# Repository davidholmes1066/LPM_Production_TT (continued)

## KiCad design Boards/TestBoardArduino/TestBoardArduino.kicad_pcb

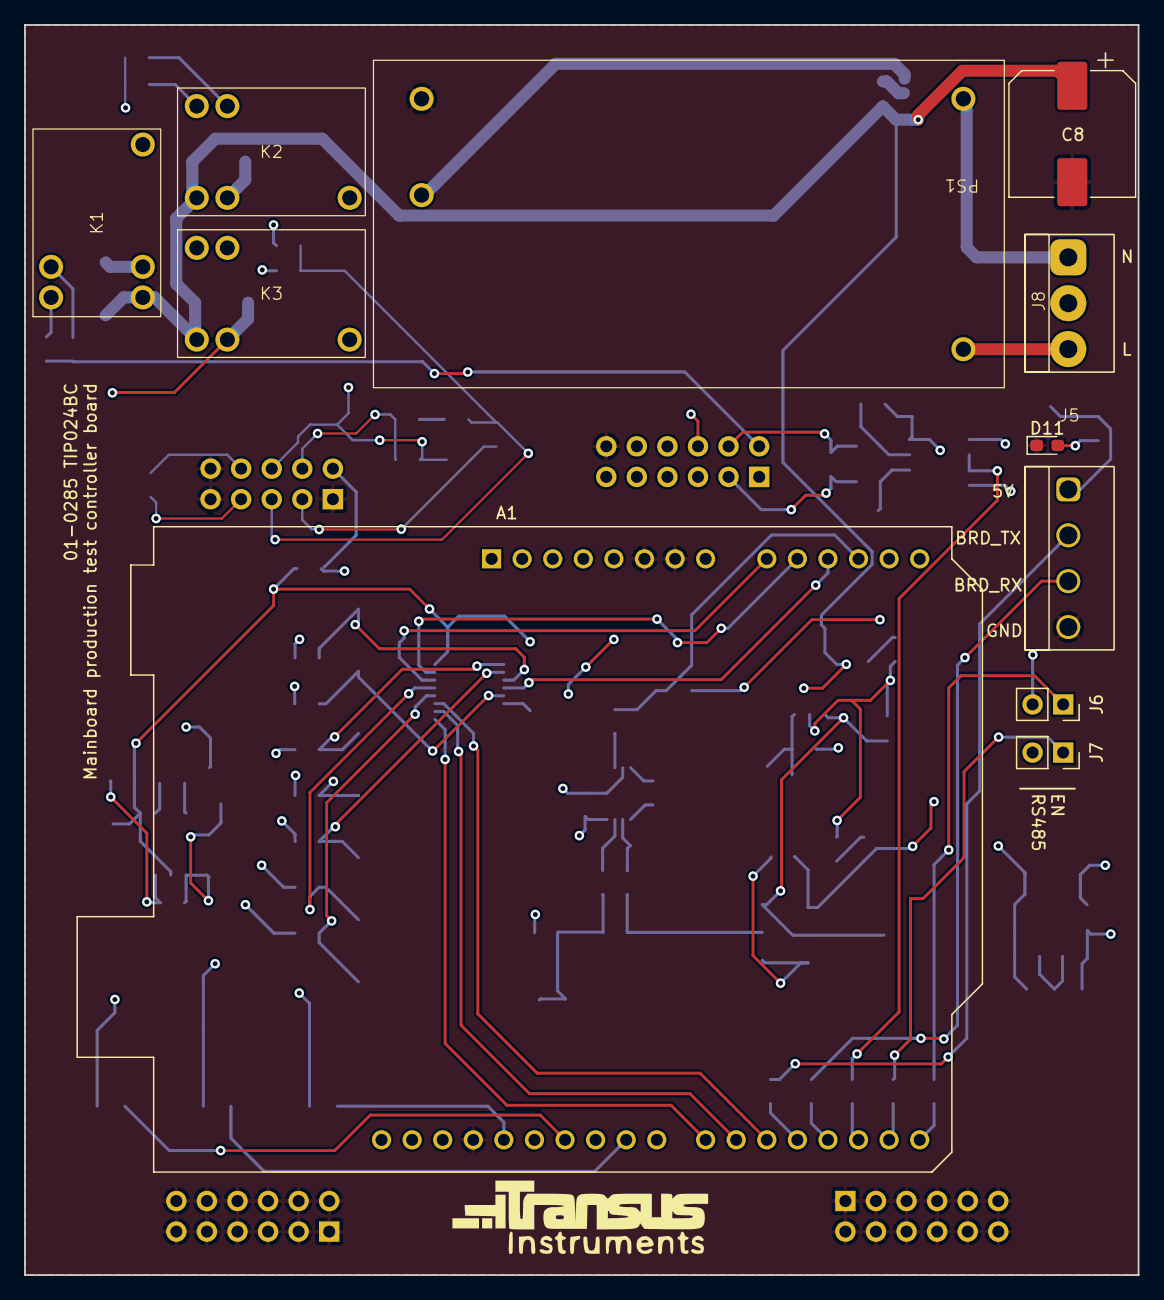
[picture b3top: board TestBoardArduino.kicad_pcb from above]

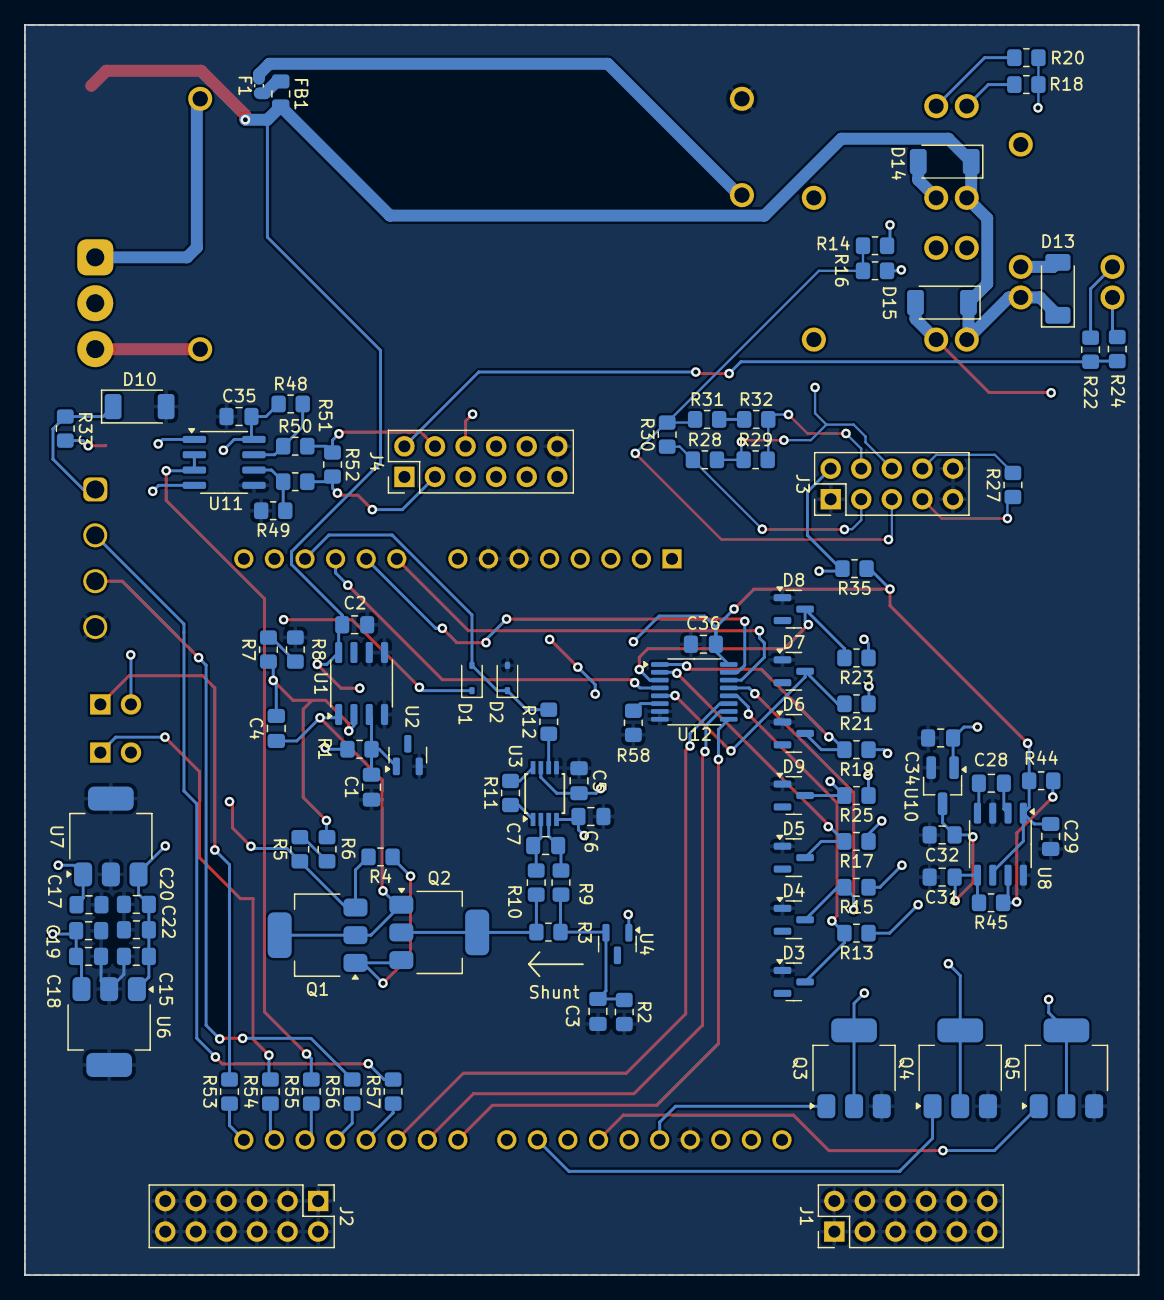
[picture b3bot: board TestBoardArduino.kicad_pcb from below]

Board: 4 copper layers, 92.5 x 103.8 mm, 111 parts (100 on the bottom side), 88 nets.

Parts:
A1: Arduino_UNO_R3
C1, C2, C5, C6: 0u1F; C_0805_2012Metric_Pad1.18x1.45mm_HandSolder
C3, C15, C35, C36: 0.1uF; C_0805_2012Metric_Pad1.18x1.45mm_HandSolder
C4: 1nF; C_0805_2012Metric_Pad1.18x1.45mm_HandSolder
C7, C18, C19, C20, C22, C29, C31, C32, C34: 10uF; C_0805_2012Metric_Pad1.18x1.45mm_HandSolder
C8: 220uF; CP_Elec_10x10
C17, C28: 1uF; C_0805_2012Metric_Pad1.18x1.45mm_HandSolder
D1, D2: D_Schottky; D_SOD-323
D3: DNM; SOT-23
D4, D5, D6, D7, D8, D9: 3v6; SOT-23
D10, D13, D14, D15: fast; D_SOD-128
D11: Green; LED_0603_1608Metric_Pad1.05x0.95mm_HandSolder
F1: 1A; Fuse_0402_1005Metric_Pad0.77x0.64mm_HandSolder
FB1: MMZ2012Y600BT000; C_0805_2012Metric_Pad1.18x1.45mm_HandSolder
J1: TU; PinHeader_2x06_P2.54mm_Vertical
J2: TD; PinHeader_2x06_P2.54mm_Vertical
J3: PT; PinHeader_2x05_P2.54mm_Vertical
J4: V+RS485; PinHeader_2x06_P2.54mm_Vertical
J5: UART; 3.81mm4PosTerm_2007987
J6, J7: 2.54mm; PinSocket_1x02_P2.54mm_Vertical
J8: 2007986; Screwterminal_3mm81_3pos
K1, K2, K3: MCHRS1KH-S DC24V; MCHRS1KH-S
PS1: IRM-15-24
Q1, Q2: BCP54TA; SOT-223-3_TabPin2
Q3, Q4, Q5: DMN6068SE-13; SOT-223-3_TabPin2
R1, R35: 10k; R_0805_2012Metric_Pad1.20x1.40mm_HandSolder
R2, R44: 100k; R_0805_2012Metric_Pad1.20x1.40mm_HandSolder
R3: 10R 0.1%; R_0805_2012Metric_Pad1.20x1.40mm_HandSolder
R4, R50, R51: 10R; R_0805_2012Metric_Pad1.20x1.40mm_HandSolder
R5: 5Meg6; R_0805_2012Metric_Pad1.20x1.40mm_HandSolder
R6, R9, R10: 160k; R_0805_2012Metric_Pad1.20x1.40mm_HandSolder
R7: 1Meg; R_0805_2012Metric_Pad1.20x1.40mm_HandSolder
R8: 210k; R_0805_2012Metric_Pad1.20x1.40mm_HandSolder
R11, R52: 120R; R_0805_2012Metric_Pad1.20x1.40mm_HandSolder
R12: 100R; R_0805_2012Metric_Pad1.20x1.40mm_HandSolder
R13, R15, R17, R19, R21, R23, R25: 1k; R_0805_2012Metric_Pad1.20x1.40mm_HandSolder
R14, R18, R24, R53, R54, R55, R56, R57, R58: 0R; R_0805_2012Metric_Pad1.20x1.40mm_HandSolder
R16, R20, R22: DNM; R_0805_2012Metric_Pad1.20x1.40mm_HandSolder
R27: 1k 0.1%; R_0805_2012Metric_Pad1.20x1.40mm_HandSolder
R28, R29, R30, R31: 2k; R_0805_2012Metric_Pad1.20x1.40mm_HandSolder
R32: 604R; R_0805_2012Metric_Pad1.20x1.40mm_HandSolder
R33: 320R; R_0805_2012Metric_Pad1.20x1.40mm_HandSolder
R45: 91k; R_0805_2012Metric_Pad1.20x1.40mm_HandSolder
R48, R49: 4k7; R_0805_2012Metric_Pad1.20x1.40mm_HandSolder
U1: MC33172; SO-8_3.9x4.9mm_P1.27mm
U2, U4: LM4040DBZ-2.5; SOT-23
U3: LT6370IMS8#PBF; TSSOP-8_3x3mm_P0.65mm
U6: LM2937IMP-5.0/NOPB; SOT-223-3_TabPin2
U7: LM2940IMP-12/NOPB; SOT-223-3_TabPin2
U8: MAX889TESA+; SO-8_3.9x4.9mm_P1.27mm
U10: XC6902N331MR-G; SOT-23_Handsoldering
U11: MAX485ECSA+; SOIC-8_3.9x4.9mm_P1.27mm
U12: CD4053B; TSSOP-16_4.4x5mm_P0.65mm

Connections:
+1.8VDD: D5.3 (K), R17.2, U12.2 (B0)
+1.8VDD_LPM: J4.7, R17.1
+1.8VIO: D8.3 (K), R23.2, U12.3 (C1)
+1.8VIO_LPM: J4.10, R23.1
+3.0VIO: D6.3 (K), R19.2, U12.1 (B1)
+3.0VIO_LPM: J4.8, R19.1
+5V: C18.1, C19.1, C29.1, C35.1, C36.1, D1.1 (K), R35.1, R44.2, R48.1, U6.3 (VO), U8.1 (IN), U8.6 (/SHDN), U11.8 (VCC), U12.16 (VDD)
+5VP: D10.1 (K), J5.1, R33.1
+12V: A1.8 (VIN), C15.1, C20.1, C22.1, U6.1 (VI), U7.3 (VO)
+24V: C2.2, C5.2, C8.1, C17.1, D13.1 (K), D14.1 (K), D15.1 (K), FB1.2, K1.3, K2.3, K3.3, R1.1, U1.8 (V+), U3.7 (V+), U4.1 (K), U7.1 (VI)
+BATT: J4.2, R22.1, R24.1
+RS485: J4.3, R51.2, R52.1
-3V3: C6.1, C34.1, U3.4 (V-), U10.1 (-VOUT)
-RS485: J4.4, R50.2, R52.2
B+: J3.5, R14.1, R16.1, R30.2, R31.1
B-: J3.6, K3.5, R28.2, R29.1
BLE_VDD: A1.13 (SDA/A4), D9.3 (K), R25.2
BLE_VDD_LPM: J4.11, R25.1
CORE_VDD: D4.3 (K), R15.2, U12.13 (A1)
CORE_VDD_LPM: J4.6, R15.1
Dout: A1.23 (D8), J3.2, R35.2
EN_BAT: A1.28 (D13), Q3.1 (G)
EN_RX/TX: R55.2, U11.2 (~RE), U11.3 (DE)
GND: A1.6 (GND), A1.7 (GND), A1.29 (GND), C1.1, C2.1, C3.2, C5.1, C6.2, C8.2, C15.2, C17.2, C18.2, C19.2, C20.2, C22.2, C29.2, C31.2, C32.2, C34.2, C35.2, C36.2, D2.2 (A), D3.1 (A), D4.1 (A), D5.1 (A), D6.1 (A), D7.1 (A), D8.1 (A), D9.1 (A), D10.2 (A), D11.1 (K), J1.1, J1.2, J1.3, J1.4, J1.5, J1.6, J1.7, J1.8, J1.9, J1.10, J1.11, J1.12, J2.1, J2.2, J2.3, J2.4, J2.5, J2.6, J2.7, J2.8, J2.9, J2.10, J2.11, J2.12, J3.1, J3.9, J3.10, J4.12, J5.4, PS1.3 (-Vo), Q3.3 (S), Q4.3 (S), Q5.3 (S), R2.2, R8.2, R49.2, R58.2, U1.4 (V-), U1.5 (+), U1.6 (-), U2.2 (A), U3.5 (Ref), U6.2 (GND), U7.2 (GND), U8.3 (GND), U8.8 (AGND), U10.2 (GND), U11.5 (GND), U12.7 (VEE), U12.8 (VSS)
IOUT: A1.12 (A3), D1.2 (A), D2.1 (K), R12.2
unnamed: A1.9 (A0), U12.14 (A)
unnamed: A1.10 (A1), U12.15 (B)
unnamed: A1.11 (A2), U12.4 (C)
unnamed: A1.15 (D0/RX), R53.1
unnamed: A1.16 (D1/TX), R54.1
unnamed: A1.17 (D2), R55.1
unnamed: A1.18 (D3), R56.1
unnamed: A1.19 (D4), R57.1
unnamed: D11.2 (A), R33.2
unnamed: D13.2 (A), K1.4, Q3.2 (D)
unnamed: D14.2 (A), K2.4, Q4.2 (D)
unnamed: D15.2 (A), K3.4, Q5.2 (D)
unnamed: F1.1, FB1.1
unnamed: J8.1, PS1.1 (AC/N)
unnamed: J8.3, PS1.2 (AC/L)
unnamed: K1.1, R24.2
unnamed: K1.2, R22.2
unnamed: K2.1, R18.2
unnamed: K2.2, R20.2
unnamed: K3.1, R14.2
unnamed: K3.2, R16.2
unnamed: F1.2, PS1.4 (+Vo)
unnamed: Q1.1 (B), Q2.3 (E), R4.1
unnamed: K1.5, Q1.3 (E), R4.2, R5.1
unnamed: C4.1, Q1.2 (C), Q2.1 (B), U1.1
unnamed: Q2.2 (C), R3.2, R10.1
unnamed: R5.2, R6.1
unnamed: R7.2, R8.1
unnamed: R31.2, R32.1
unnamed: C1.2, R1.2, U1.3 (+), U2.1 (K)
unnamed: C4.2, R6.2, R7.1, U1.2 (-)
unnamed: C7.1, R9.2, U3.3 (IN+)
unnamed: C7.2, R10.2, U3.2 (IN-)
unnamed: R12.1, U3.6 (OUT)
unnamed: R11.2, U3.8 (Rg+)
unnamed: R11.1, U3.1 (Rg-)
unnamed: C3.1, R2.1, R3.1, R9.1, U4.2 (A)
unnamed: C28.1, U8.2 (CAP+)
unnamed: C28.2, U8.4 (CAP-)
unnamed: R44.1, R45.1, U8.7 (FB)
unnamed: C31.1, C32.1, R45.2, U8.5 (OUT), U10.3 (-IN)
unnamed: R49.1, R51.1, U11.6 (A)
unnamed: R48.2, R50.1, U11.7 (B)
unnamed: R58.1, U12.6 (INH)
RX: J6.2, U11.1 (RO)
S1: A1.20 (D5), U12.11 (S1)
S2: A1.21 (D6), U12.10 (S2)
S3: A1.22 (D7), U12.9 (S3)
SHRT_P: A1.26 (D11), Q5.1 (G)
SHRT_T: A1.24 (D9), Q4.1 (G)
T+: J3.7, R18.1, R20.1, R27.1
T-: J3.8, K2.5, R27.2
TX: J7.2, U11.4 (DI)
UART_RX: J6.1, R53.2
UART_S_RX: J5.3, R56.2
UART_S_TX: J5.2, R57.2
UART_TX: J7.1, R54.2
VB+: J3.3, R28.1, R30.1
VB-: J3.4, R29.2, R32.2
VCC_MAIN: D3.3 (K), R13.2, U12.12 (A0)
VCC_MAIN_LPM: J4.5, R13.1
VPP_2V5: D7.3 (K), R21.2, U12.5 (C0)
VPP_2V5_LPM: J4.9, R21.1

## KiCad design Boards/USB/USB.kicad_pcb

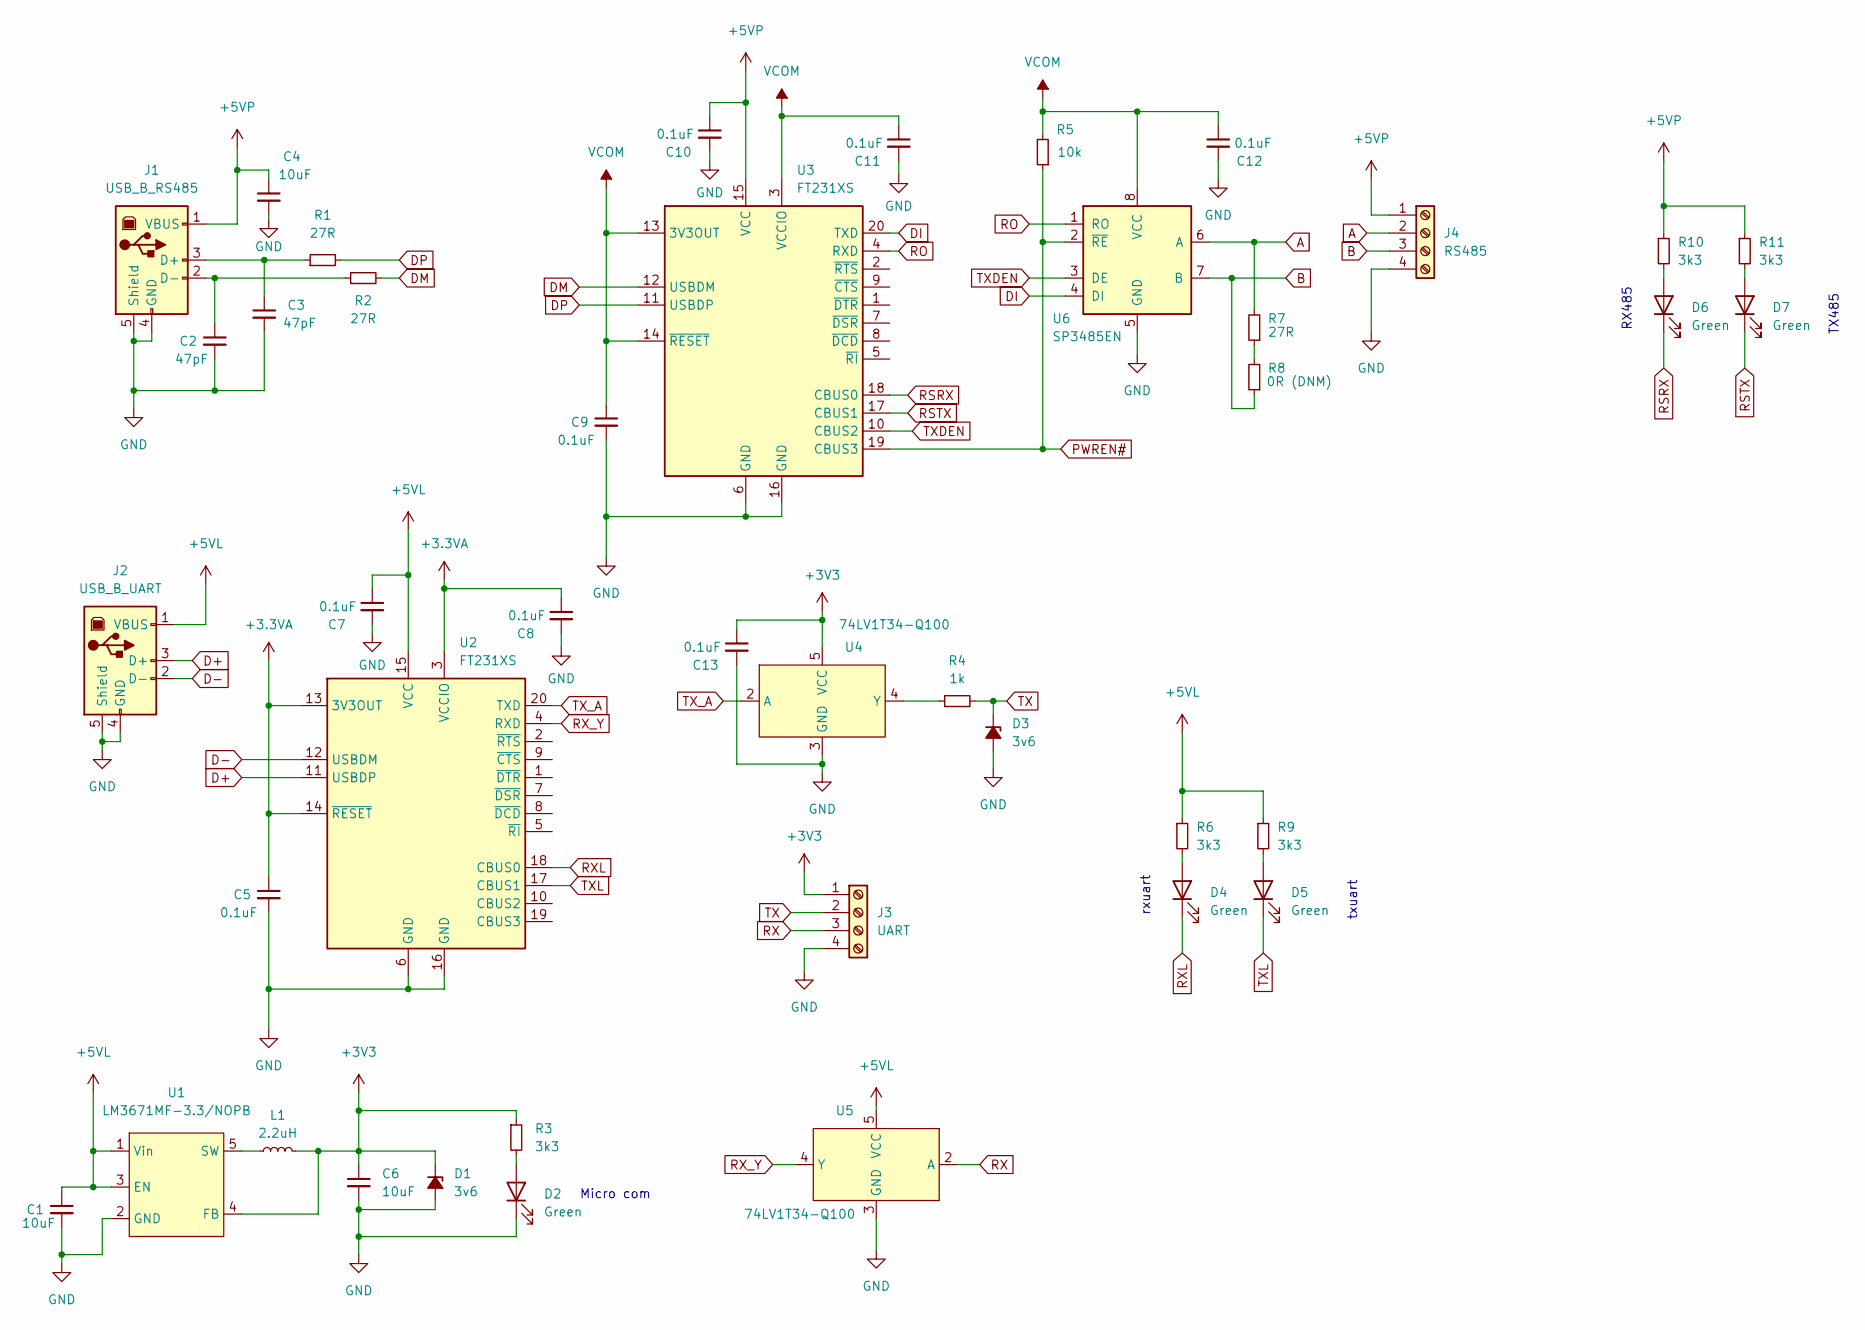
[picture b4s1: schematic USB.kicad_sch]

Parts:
C1, C4, C6: 10uF; C_0805_2012Metric_Pad1.18x1.45mm_HandSolder
C2, C3: 47pF; C_0805_2012Metric_Pad1.18x1.45mm_HandSolder
C5, C7, C8, C9, C10, C11, C12, C13: 0.1uF; C_0805_2012Metric_Pad1.18x1.45mm_HandSolder
D1, D3: 3v6; BZX84C3V6; Farnell 1902466
D2, D4, D5, D6, D7: Green; LED_0402_1005Metric_Pad0.77x0.64mm_HandSolder; Farnell 2507544
J1: USB_B_RS485; USB_B
J2: USB_B_UART; USB_B
J3: UART; Screwterminal_3mm81_4pos
J4: RS485; Screwterminal_3mm81_4pos
L1: 2.2uH; 0805_PInductor; Farnell 3865051
R1, R2, R7: 27R; R_0805_2012Metric_Pad1.20x1.40mm_HandSolder
R3, R6, R9, R10, R11: 3k3; R_0805_2012Metric_Pad1.20x1.40mm_HandSolder
R4: 1k; R_0805_2012Metric_Pad1.20x1.40mm_HandSolder
R5: 10k; R_0805_2012Metric_Pad1.20x1.40mm_HandSolder
R8: 0R (DNM); R_0805_2012Metric_Pad1.20x1.40mm_HandSolder
U1: LM3671MF-3.3/NOPB; SOT-23-5_HandSoldering; Farnell 3008192
U2, U3: FT231XS; SSOP-20_3.9x8.7mm_P0.635mm
U4, U5: 74LV1T34-Q100; 74LV1T34GV-Q100H
U6: SP3485EN; SOIC-8_3.9x4.9mm_P1.27mm

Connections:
+3.3VA: C5.1, C8.1, U2.3 (VCCIO), U2.13 (3V3OUT), U2.14 (~RESET)
+3V3: C6.1, C13.1, D1.1 (K), J3.1, L1.2, R3.1, U1.4 (FB), U4.5 (VCC)
+5VL: C1.1, C7.1, J2.1 (VBUS), R6.1, R9.1, U1.1 (Vin), U1.3 (EN), U2.15 (VCC), U5.5 (VCC)
+5VP: C4.1, C10.1, J1.1 (VBUS), J4.1, R10.1, R11.1, U3.15 (VCC)
A: J4.2, R7.2, U6.6 (A)
B: J4.3, R8.1, U6.7 (B)
D+: J2.3 (D+), U2.11 (USBDP)
D-: J2.2 (D-), U2.12 (USBDM)
DI: U3.20 (TXD), U6.4 (DI)
DM: R2.2, U3.12 (USBDM)
DP: R1.2, U3.11 (USBDP)
GND: C1.2, C2.2, C3.2, C4.2, C5.2, C6.2, C7.2, C8.2, C9.2, C10.2, C11.2, C12.2, C13.2, D1.2 (A), D2.1 (K), D3.2 (A), J1.4 (GND), J1.5 (Shield), J2.4 (GND), J2.5 (Shield), J3.4, J4.4, U1.2 (GND), U2.6 (GND), U2.16 (GND), U3.6 (GND), U3.16 (GND), U4.3 (GND), U5.3 (GND), U6.5 (GND)
unnamed: D2.2 (A), R3.2
unnamed: D4.2 (A), R6.2
unnamed: D5.2 (A), R9.2
unnamed: D6.2 (A), R10.2
unnamed: D7.2 (A), R11.2
unnamed: C2.1, J1.2 (D-), R2.1
unnamed: C3.1, J1.3 (D+), R1.1
unnamed: L1.1, U1.5 (SW)
unnamed: R4.1, U4.4 (Y)
unnamed: R7.1, R8.2
PWREN#: R5.1, U3.19 (CBUS3), U6.2 (~RE)
RO: U3.4 (RXD), U6.1 (RO)
RSRX: D6.1 (K), U3.18 (CBUS0)
RSTX: D7.1 (K), U3.17 (CBUS1)
RX: J3.3, U5.2 (A)
RXL: D4.1 (K), U2.18 (CBUS0)
RX_Y: U2.4 (RXD), U5.4 (Y)
TX: D3.1 (K), J3.2, R4.2
TXDEN: U3.10 (CBUS2), U6.3 (DE)
TXL: D5.1 (K), U2.17 (CBUS1)
TX_A: U2.20 (TXD), U4.2 (A)
VCOM: C9.1, C11.1, C12.1, R5.2, U3.3 (VCCIO), U3.13 (3V3OUT), U3.14 (~RESET), U6.8 (VCC)

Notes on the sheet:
rxuart
Micro com
RX485
TX485
txuart

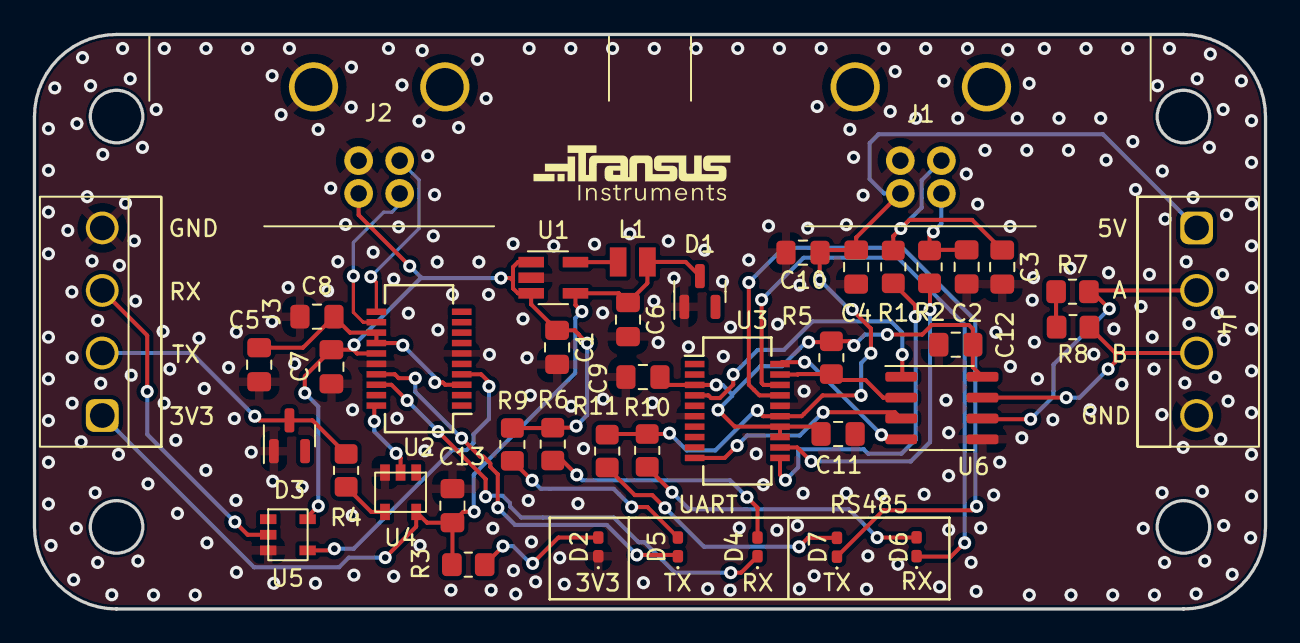
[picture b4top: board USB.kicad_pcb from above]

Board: 2 copper layers, 75.0 x 35.0 mm, 42 parts (0 on the bottom side), 34 nets.

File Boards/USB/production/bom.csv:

Designator,Footprint,Quantity,Value,LCSC Part #
"C1, C4, C6",C_0805_2012Metric_Pad1.18x1.45mm_HandSolder,3,10uF,
"C10, C11, C12, C13, C5, C7, C8, C9",C_0805_2012Metric_Pad1.18x1.45mm_HandSolder,8,0.1uF,
"C2, C3",C_0805_2012Metric_Pad1.18x1.45mm_HandSolder,2,47pF,
"D1, D3",BZX84C3V6,2,3v6,
"D2, D4, D5, D6, D7",LED_0402_1005Metric_Pad0.77x0.64mm_HandSolder,5,Green,
J1,USB_B,1,USB_B_RS485,
J2,USB_B,1,USB_B_UART,
J3,Screwterminal_3mm81_4pos,1,UART,
J4,Screwterminal_3mm81_4pos,1,RS485,
L1,0805_PInductor,1,2.2uH,
"R1, R2, R7",R_0805_2012Metric_Pad1.20x1.40mm_HandSolder,3,27R,
"R10, R11, R3, R6, R9",R_0805_2012Metric_Pad1.20x1.40mm_HandSolder,5,3k3,
R4,R_0805_2012Metric_Pad1.20x1.40mm_HandSolder,1,1k,
R5,R_0805_2012Metric_Pad1.20x1.40mm_HandSolder,1,10k,
R8,R_0805_2012Metric_Pad1.20x1.40mm_HandSolder,1,0R (DNM),
U1,SOT-23-5_HandSoldering,1,LM3671MF-3.3/NOPB,
"U2, U3",SSOP-20_3.9x8.7mm_P0.635mm,2,FT231XS,
"U4, U5",74LV1T34GV-Q100H,2,74LV1T34-Q100,
U6,SOIC-8_3.9x4.9mm_P1.27mm,1,SP3485EN,

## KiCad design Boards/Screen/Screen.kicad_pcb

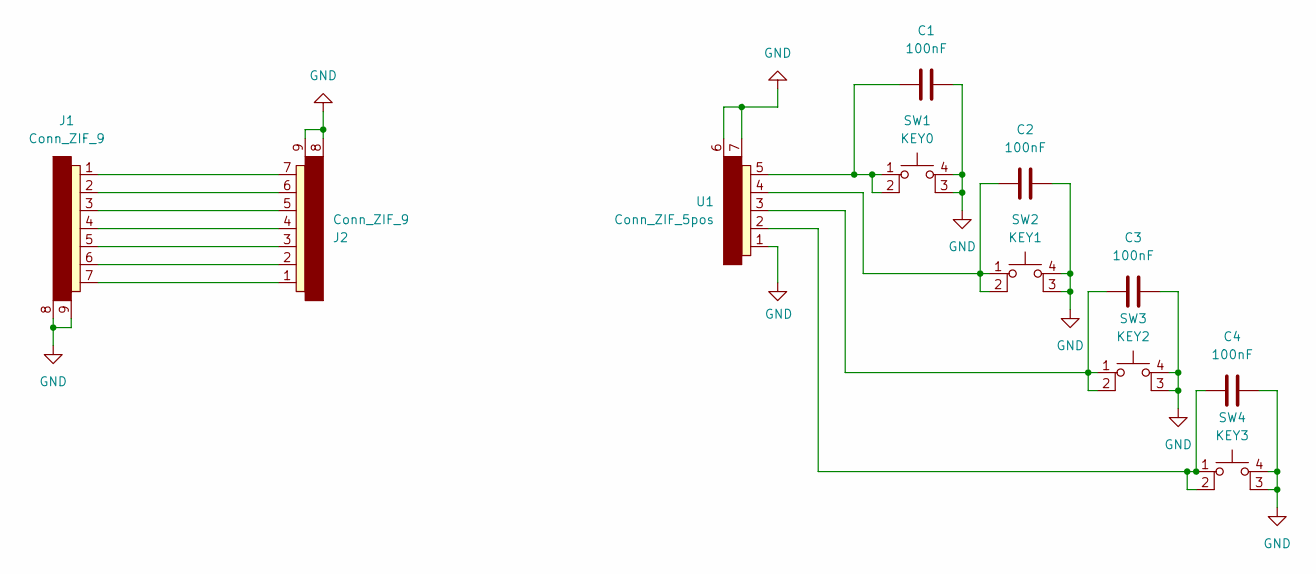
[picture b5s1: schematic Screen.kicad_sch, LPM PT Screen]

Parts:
C1, C2, C3, C4: 100nF; C_0805_2012Metric_Pad1.18x1.45mm_HandSolder
J1, J2: Conn_ZIF_9; Conn_ZIF_7pos
SW1: KEY0; Tactile_button_Frn1775334
SW2: KEY1; Tactile_button_Frn1775334
SW3: KEY2; Tactile_button_Frn1775334
SW4: KEY3; Tactile_button_Frn1775334
U1: Conn_ZIF_5pos

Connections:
GND: C1.2, C2.2, C3.2, C4.2, J1.8, J1.9, J2.8, J2.9, SW1.3 (K), SW1.4 (A), SW2.3 (K), SW2.4 (A), SW3.3 (K), SW3.4 (A), SW4.3 (K), SW4.4 (A), U1.1, U1.6, U1.7
unnamed: C1.1, SW1.1, SW1.2, U1.5
unnamed: C2.1, SW2.1, SW2.2, U1.4
unnamed: J1.1, J2.7
unnamed: J1.2, J2.6
unnamed: J1.3, J2.5
unnamed: J1.4, J2.4
unnamed: J1.5, J2.3
unnamed: J1.6, J2.2
unnamed: J1.7, J2.1
unnamed: C4.1, SW4.1, SW4.2, U1.2
unnamed: C3.1, SW3.1, SW3.2, U1.3

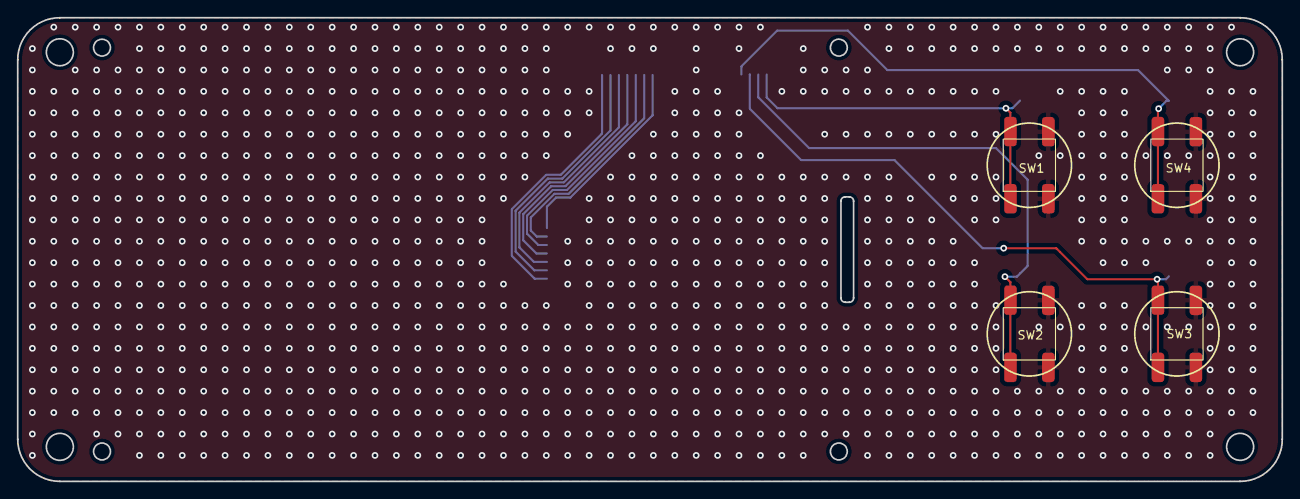
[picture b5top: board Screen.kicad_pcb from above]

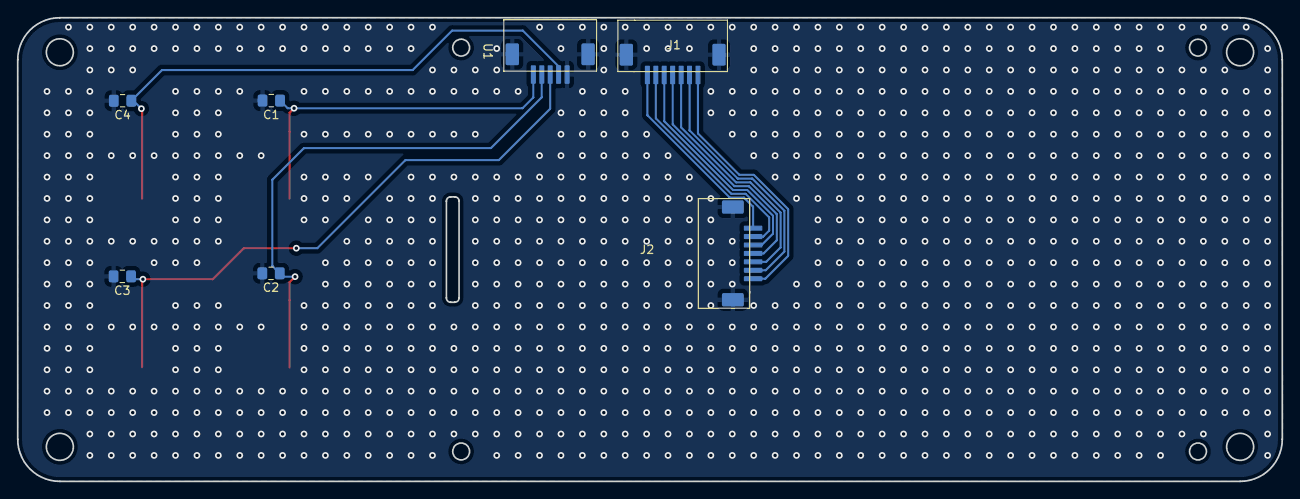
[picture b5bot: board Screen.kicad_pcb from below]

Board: 2 copper layers, 150.0 x 55.0 mm, 11 parts (7 on the bottom side), 12 nets.

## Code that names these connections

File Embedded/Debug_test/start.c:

/*
 * init.c
 *
 * Created: 18/05/2022 12:26:41
 *  Author: david
 */ 

#include <stdio.h>
#include <stdio.h>
#include "start.h"

void init_UART(void)
{
	PORTE_DIRCLR = PIN2_bm;												//Set RX pin USARTE0 E2 as input
	PORTE_DIRSET = PIN3_bm;												//Set TX pin USARTE0 E3 as output
	PORTE_OUTSET = PIN3_bm;												//Set TX pin to high
	
	USARTE0.BAUDCTRLB |= (0x09<<4);										//Set BSCALE to -7 for baud 115200
	USARTE0.BAUDCTRLA |= (0x2E);										//Set BSEL to 2094 for baud 115200
	USARTE0.BAUDCTRLB |= (0x08);										//Set BSel to 2094 for baud 115200
	
	USARTE0.CTRLC |= (0x03);											//Sets amount of data bits to 8
	USARTE0.CTRLB |= (0x03<<3);											//Sets the Rx and TX enable bits.
}

void init_CLK(void)
{
	OSC.CTRL |= OSC_RC32MEN_bm;											// Enable internal 32 MHz oscillator
	while(!(OSC.STATUS & OSC_RC32MRDY_bm));								// Wait for oscillator is ready
	CCP = CCP_IOREG_gc;													// Security signature to modify clock
	CLK.CTRL = CLK_SCLKSEL_RC32M_gc;									// Select 32 MHz oscillator
	CLK.PSCTRL = CLK_PSADIV_1_gc;										// Set PSA to 1
	CLK.PSCTRL = CLK_PSBCDIV_1_1_gc;									// Set PSB&PSC to 1
}

void init_TIMER(void)
{
	TCE0.CTRLB = TC_WGMODE_NORMAL_gc;									//Set timer E0 to normal mode
	TCE0.CTRLA = TC_CLKSEL_OFF_gc;										//Timer is off until clksel is changed
	TCE0.INTCTRLA = TC_OVFINTLVL_LO_gc;									//Set overflow interrupt TCE0 to low level
	TCE0.PERL = 0xFF;
	TCE0.PERH = 0xFF;													//t = N*(PER + 1)/F_CPU = 0.25
}

void init_DELAY(void)													//Uses two 16Bit TC's to form 32 Bit one
{
	TCD1.CTRLB = TC_WGMODE_NORMAL_gc;									//Set timer E0 to normal mode
	TCD1.CTRLA = TC_CLKSEL_OFF_gc;										//Timer is off until clksel is changed
	TCD1.PER = 0xFFFF;													//t = N*(PER + 1)/F_CPU = 0.25
}

void init_ADC(void)
{
	PORTA_DIRCLR = PIN0_bm;												//VCC_main
	PORTA_DIRCLR = PIN1_bm;												//CORE_VDD
	PORTA_DIRCLR = PIN2_bm;												//+1.8VDD
	PORTA_DIRCLR = PIN3_bm;												//+3.0VIO
	PORTA_DIRCLR = PIN4_bm;												//I_external
	PORTA_DIRCLR = PIN5_bm;												//I_battery
	
	PORTB_DIRCLR = PIN0_bm;												//VPP_2V5
	PORTB_DIRCLR = PIN1_bm;												//+1.8VIO
	PORTB_DIRCLR = PIN4_bm;												//BLE_VDD
	PORTB_DIRCLR = PIN5_bm;												//D0 samples
	PORTB_DIRCLR = PIN6_bm;												//D1 samples
	
	//ADCA.PRESCALER |= ADC_PRESCALER_DIV8_gc;							//Set ADCA clock speed to 62.5kHz
	//ADCB.PRESCALER |= ADC_PRESCALER_DIV8_gc;							//Set ADCB clock speed to 62.5kHz
	ADCA.PRESCALER = ADC_PRESCALER_DIV32_gc;							//2MHz system clock use: ADCA clock speed to 62.5kHz
	ADCB.PRESCALER = ADC_PRESCALER_DIV32_gc;							//2MHz system clock use: ADCB clock speed to 62.5kHz
	
	ADCA.REFCTRL |= ADC_RESOLUTION_12BIT_gc;							//Set ADCA to 12bit resolution
	ADCB.REFCTRL |= ADC_RESOLUTION_12BIT_gc;							//Set ADCB to 12bit resolution
	
	ADCA.REFCTRL |= ADC_REFSEL_INTVCC_gc;								//Set ADCA reference voltage to internal VCC
	ADCB.REFCTRL |= ADC_REFSEL_INTVCC_gc;								//Set ADCB reference voltage to internal VCC
	
	ADCA.CH0.CTRL |= ADC_CH_INPUTMODE_SINGLEENDED_gc;					//Set ADCA channel 0 differential input
	ADCA.CH1.CTRL |= ADC_CH_INPUTMODE_SINGLEENDED_gc;					//Set ADCA channel 1 differential input
	ADCA.CH2.CTRL |= ADC_CH_INPUTMODE_SINGLEENDED_gc;					//Set ADCA channel 2 differential input
	ADCA.CH3.CTRL |= ADC_CH_INPUTMODE_SINGLEENDED_gc;					//Set ADCA channel 3 differential input
	
	ADCB.CH0.CTRL |= ADC_CH_INPUTMODE_SINGLEENDED_gc;					//Set ADCB channel 0 differential input
	ADCB.CH1.CTRL |= ADC_CH_INPUTMODE_SINGLEENDED_gc;					//Set ADCB channel 1 differential input
	ADCB.CH2.CTRL |= ADC_CH_INPUTMODE_SINGLEENDED_gc;					//Set ADCB channel 2 differential input
	ADCB.CH3.CTRL |= ADC_CH_INPUTMODE_SINGLEENDED_gc;					//Set ADCB channel 3 differential input
	
	ADCA.CH0.MUXCTRL |= ADC_CH_MUXNEG_INTGND_MODE3_gc;					//Set ADCA channel 0 reference voltage to internal GND
	ADCA.CH1.MUXCTRL |= ADC_CH_MUXNEG_INTGND_MODE3_gc;					//Set ADCA channel 1 reference voltage to internal GND
	ADCA.CH2.MUXCTRL |= ADC_CH_MUXNEG_INTGND_MODE3_gc;					//Set ADCA channel 2 reference voltage to internal GND
	ADCA.CH3.MUXCTRL |= ADC_CH_MUXNEG_INTGND_MODE3_gc;					//Set ADCA channel 3 reference voltage to internal GND
	
	ADCB.CH0.MUXCTRL |= ADC_CH_MUXNEG_INTGND_MODE3_gc;					//Set ADCB channel 0 reference voltage to internal GND
	ADCB.CH1.MUXCTRL |= ADC_CH_MUXNEG_INTGND_MODE3_gc;					//Set ADCB channel 1 reference voltage to internal GND
	ADCB.CH2.MUXCTRL |= ADC_CH_MUXNEG_INTGND_MODE3_gc;					//Set ADCB channel 2 reference voltage to internal GND
	ADCB.CH3.MUXCTRL |= ADC_CH_MUXNEG_INTGND_MODE3_gc;					//Set ADCB channel 3 reference voltage to internal GND
}

#ifndef dis_dac
void init_DAC(void)
{
	DACB.CTRLC = DAC_REFSEL_INT1V_gc;									//set DAC reference to internal 1V
	DACB.CTRLB = DAC_CHSEL_DUAL_gc;										//set DAC to DUAL channel mode
	DACB.CTRLA = DAC_CH1EN_bm | DAC_CH0EN_bm | DAC_ENABLE_bm;			//Enable both DAC channels
	// PINS: PB2 = DACCH0 & PB3 = DACCH1
	// Write: to register DACB.CH0DATA and DACB.CH1DATA
}
#endif

void init_supply(void)
{
	PORTB_DIRSET = PIN2_bm;												//Set pin as output to enable ... supply
	PORTB_DIRSET = PIN3_bm;												//Set pin as output to enable ... supply
}

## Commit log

2023-02-11 Added Board-,embedded and matlab gui files
2023-02-13 Added excel to gui
2023-03-22 Figuring out why supply cal not working
2023-05-09 ReadVolt converted to floats
    Will still need to convert some of the other functions to be standalone
2023-06-29 Added python code
2023-07-04 latest
2024-06-26 added relay
    Still needs better separation between the AC lines and footprints relay need fixing
2024-07-11 Updated board
